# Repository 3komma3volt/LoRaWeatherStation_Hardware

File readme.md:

# LoRa Weather Station

The project was born for testing LoRa devices an has grown to a small weather station ecosystem.
Since August 2002, there are 6 station outside running without any maintenance. 

## Features

 - Completely 3D printed main body
 - Modular with optional extension
 - Simple PCB which can be hand assembled
 - Stations can be equipped with sensors as needed, they don't have to be the same kind
 - Using TheThingsStack for receiving data
 - Storage and analysis of data using a PHP framework (other repository)

## Housing

The main housing consists of:
 - Main housing
 - Front door
 - Sensor cover **or** light sensor mount
 - 2x side dust filter fixture
 - Front door dust filter fixture

On the sides and in the front door, there is the possibility to mount some 3mm fleece filters to prevent dust going into the housing and keep bugs out. A disadvantage is, that the inside gets a bit hotter if exposed to the sun.
The best mounting position of the station is 2m from the ground facing north and protected from sun exposure (The solar cell will get enough light to charge the battery).
A 80x55mm 7V solar cell is used to charge the battery. The solar cell is glued to the main body using silicone glue. This works great to keep rain out,
On the bottom is a intended breaking point to mount 12mm screw connectors for external sensors e.g. rain sensor or wind direction sensor.
On the left side is a hole for mounting a SMA connector for the LoRa antenna.
The housing can be mounted on a wall using a hook or screw.

## PCB
The PCB is kept simple, so it can be assembled by hand. It has to be screwed into the main body using **M3x8** (or similar length, there is plenty of space for longer screws)

It is possible to use it just as carrier board, in this case, no component needs to be assembled.
For easier installation, XH connectors are used to connect sensors, battery, solar cell etc.
The CubeCell AB01 board is the brain of the weather station. It has a battery connector on its bottom side. For easier replacement of board or battery, this connector is connected with the PCB which again connects to the battery.
A BME280 board is connected using a standard header, so it can be replaced easily.

Two holes on the lower side of the PCB are for mounting a lithium battery using zip ties.
A  standard 1000mA 3.7V LIPO battery works great and never ran out even on cold and dark winter weeks.

## Wind Direction Sensor

The wind direction sensor uses 8 reed contacts, a I2C port expander, a bearing (**608ZZ**) and a paddle to read the wind direction.

Only the expander and some few components need to be assembled.

The reed contacts are pushed through the sensor main body, On the upper side, a short wire has to be soldered to the reed contact and threaded through the second hole. The sensor and wire are then soldered to the sensor PCB.
A ⌀6x3mm magnet is glued into the sensor pin.

## Wind Speed Sensor

The wind speed sensor using the same style bearing and manget like the direction sensor. It only consists of one reed contact. 
This sensor is an early alpha state, because the baring is to difficult to move and won't turn on low wind speeds. Maybe switching to a off-the-shelf product for this use case.

## Rain sensor

The 3D printed version of a rain sensor was not reliable enough. A cheap off the shelf sensor which is sold as spare part for weather stations works well. 

## Light sensor

A VEML7700 can be mounted on the side of the main body. For this print the mount and install the sensor within the mount. Fill up the space with transparent silicone. It will get watertight and works well. 

# Firmware
The firmware is made using PlatformIO and the Heltec development platform.
Simply open with VSCode and edit the platform.ini
You can change following build flags:

- ENABLE_RAINSENSOR=0 ; enables the rain drip sensor
- ENABLE_BRIGHTNESSENSOR=1 ; enables the brightness sensor
- ENABLE_WINDDIRSENSOR=0 ; enables the wind direction sensor
- ENABLE_WINDSPEEDSENSOR=0 ; enables the winds speed sensor
- DEBUG_UART=0  ; enables UART data sending for debug purposes

Enable the functionalities as wanted. 

>  Wind speed and direction are BETA!

As brightness sensor the VEML7700 is used. The BH1750 was also tested, but the results with this sensor were not really great. It was not really possible to get the cheap housing with the light dome watertight and several sensors died after a few days. If you want to use the BH1750, some changes in the code are necessary since this parts were removed.

Then hook up with TheThingsStack. There add a new device and get the neccessary data for OTAA transmission. Insert the information in the src/ttnparams.h file.

You probably will need a payload formatter for each individual weather station, since not all stations must have the same functionallity.

Here is a example formatter:

    function Decoder(bytes, port) {
    var temperature = (bytes[0] << 8 | bytes[1]);
	var humidity = (bytes[2] << 8 | bytes[3]);
    var pressure = ((bytes[4]) << 24) + ((bytes[5]) <<  16) + ((bytes[6]) << 8) + ((bytes[7]));
    var battery = (bytes[8] << 8) | bytes[9];
    var unused = (bytes[10] << 8) | bytes[11]; // formally used for battery percent calculation
    var brightness = (bytes[12] << 8) | bytes[13];
    var rain = bytes[14];
  
    var lux = brightness * 2.1504; // Datasheet: Gain 1/8, 25ms integration time
    lux = Math.round(6.0135e-13 * Math.pow(lux, 4) - 9.3924e-9 * Math.pow(lux, 3) + 8.1488e-5 * Math.pow(lux, 2) + 1.0023 * lux);
 
    var sensorSqure = 10.9 * 4.9; // for round rain sensors: sensorSqure = Math.PI * pow(sensorRadius, 2);
    var tipsPer100ml = 100 / 1.5;
    var mlPerTip = 100 / $tipsPer100ml;
    var rainAmount = $mlPerTip / $sensorSqure;
  
    return {
      temperature: temperature / 100,
      humidity: humidity,
      pressure: pressure / 100,
      battery: battery / 1000,
      brightness: lux,
      rain: rainAmount
      }
    }

If a station doesnt have a specific feature, just remove it from the return. The value has to be null to indicate, that the sensor is not available.

Example formatter for the most basic station just with a BME280:

    function Decoder(bytes, port) {
    var temperature = (bytes[0] << 8 | bytes[1]);
	var humidity = (bytes[2] << 8 | bytes[3]);
    var pressure = ((bytes[4]) << 24) + ((bytes[5]) <<  16) + ((bytes[6]) << 8) + ((bytes[7]));
    var battery = (bytes[8] << 8) | bytes[9];
    var unused = (bytes[10] << 8) | bytes[11]; // formally used for battery percent calculation

    return {
      temperature: temperature / 100,
      humidity: humidity,
      pressure: pressure / 100,
      battery: battery / 1000,
      }
    }

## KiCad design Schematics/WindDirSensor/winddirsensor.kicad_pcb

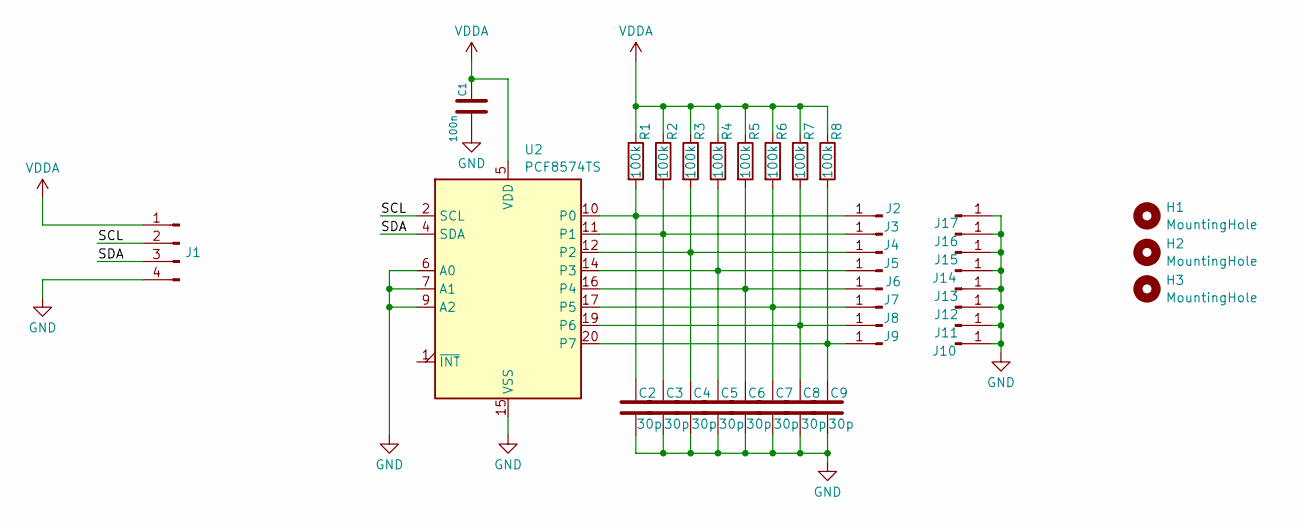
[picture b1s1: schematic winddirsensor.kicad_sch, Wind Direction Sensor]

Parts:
C1: 100n; C_0603_1608Metric; LCSC C14663
C2, C3, C4, C5, C6, C7, C8, C9: 30p; C_0603_1608Metric_Pad1.08x0.95mm_HandSolder; LCSC C1658
H1, H2, H3: MountingHole; MountingHole_3.2mm_M3
J1: Conn_01x04_Pin; JST_XH_B4B-XH-A_1x04_P2.50mm_Vertical
J2, J3, J4, J5, J6, J7, J8, J9, J10, J11, J12, J13, J14, J15, J16, J17: Conn_01x01_Pin; TestPoint_THTPad_D1.5mm_Drill0.7mm
R1, R2, R3, R4, R5, R6, R7, R8: 100k; R_0603_1608Metric; LCSC C25803
U2: PCF8574TS; SSOP-20_4.4x6.5mm_P0.65mm

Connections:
/SCL: J1.2, U2.2 (SCL)
/SDA: J1.3, U2.4 (SDA)
GND: C1.2, C2.2, C3.2, C4.2, C5.2, C6.2, C7.2, C8.2, C9.2, J1.4, J10.1, J11.1, J12.1, J13.1, J14.1, J15.1, J16.1, J17.1, U2.6 (A0), U2.7 (A1), U2.9 (A2), U2.15 (VSS)
unnamed: C2.1, J2.1, R1.2, U2.10 (P0)
unnamed: C3.1, J3.1, R2.2, U2.11 (P1)
unnamed: C4.1, J4.1, R3.2, U2.12 (P2)
unnamed: C5.1, J5.1, R4.2, U2.14 (P3)
unnamed: C6.1, J6.1, R5.2, U2.16 (P4)
unnamed: C7.1, J7.1, R6.2, U2.17 (P5)
unnamed: C8.1, J8.1, R7.2, U2.19 (P6)
unnamed: C9.1, J9.1, R8.2, U2.20 (P7)
VDDA: C1.1, J1.1, R1.1, R2.1, R3.1, R4.1, R5.1, R6.1, R7.1, R8.1, U2.5 (VDD)

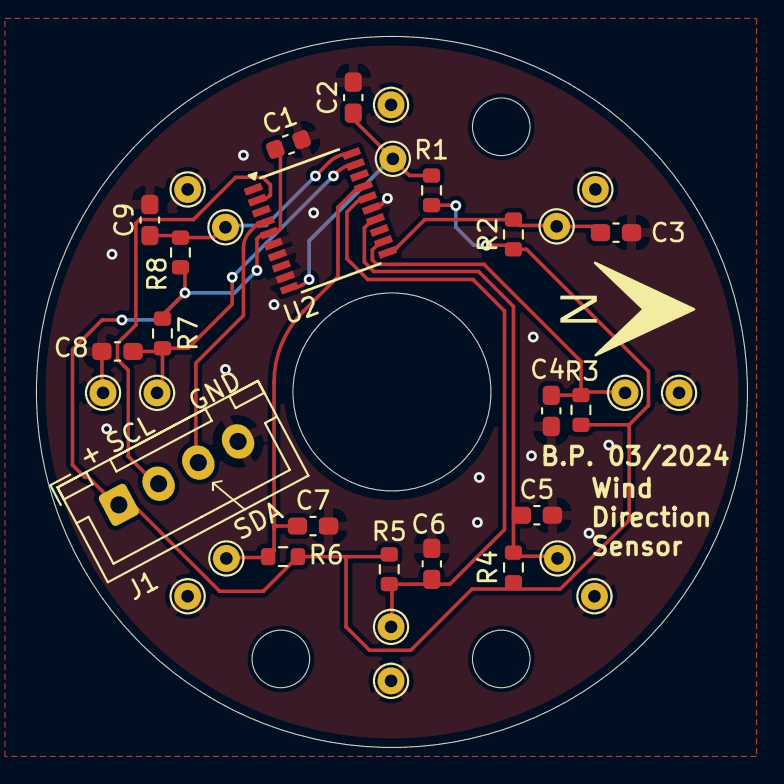
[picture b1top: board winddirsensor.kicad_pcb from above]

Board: 2 copper layers, 39.5 x 39.5 mm, 38 parts (0 on the bottom side), 12 nets.

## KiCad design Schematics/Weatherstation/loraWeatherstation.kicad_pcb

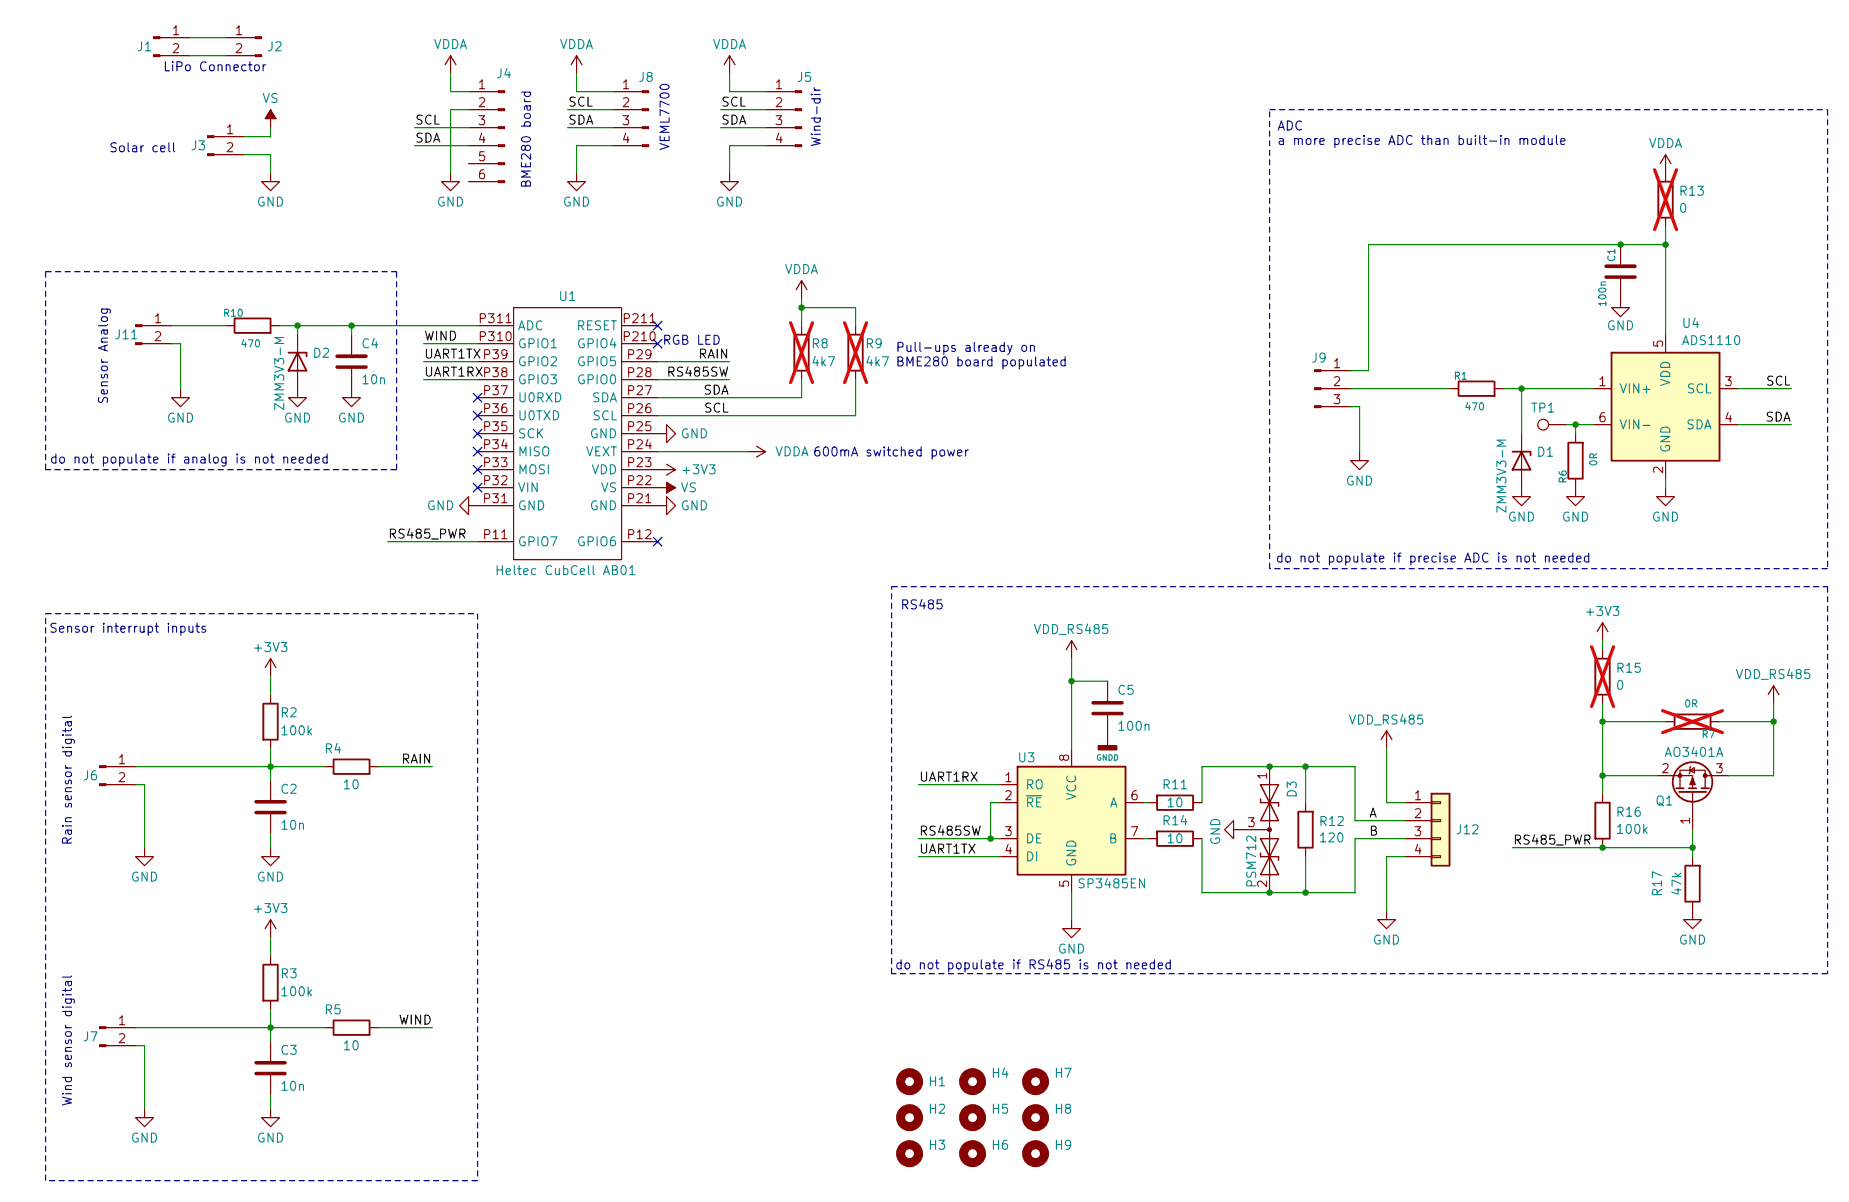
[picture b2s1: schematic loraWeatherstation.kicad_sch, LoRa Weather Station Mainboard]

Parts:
C1, C5: 100n; C_0603_1608Metric; LCSC C14663
C2, C3, C4: 10n; C_0603_1608Metric; LCSC C57112
D1, D2: ZMM3V3-M; D_MiniMELF; LCSC C8056
D3: PSM712; SOT-23; LCSC C32677
H1, H2, H3, H4, H5, H6: MountingHole; MountingHole_3.2mm_M3
H7, H8, H9: MountingHole; MountingHole_2.7mm
J1, J2, J3, J6, J7, J11: Conn_01x02_Pin; JST_XH_B2B-XH-A_1x02_P2.50mm_Vertical
J4: Conn_01x06_Pin; PinSocket_1x06_P2.54mm_Vertical
J5, J8: Conn_01x04_Pin; JST_XH_B4B-XH-A_1x04_P2.50mm_Vertical
J9: Conn_01x03_Pin; JST_XH_B3B-XH-A_1x03_P2.50mm_Vertical
J12: Conn_01x04; JST_XH_B4B-XH-A_1x04_P2.50mm_Vertical
Q1: AO3401A; SOT-23; LCSC C15127
R1, R10: 470; R_0603_1608Metric; LCSC C23182
R2, R3: 100k; R_0603_1608Metric; LCSC C25803
R4, R5, R11, R14: 10; R_0603_1608Metric; LCSC C22859
R6: 0R; R_0603_1608Metric
R7: 0R; R_0603_1608Metric; not fitted
R8, R9: 4k7; R_0603_1608Metric; LCSC C23162; not fitted
R12: 120; R_0603_1608Metric; LCSC C22787
R13, R15: 0; R_0603_1608Metric; not fitted
R16: 100k; R_0603_1608Metric; LCSC C22936
R17: 47k; R_0603_1608Metric; LCSC C25819
TP1: TestPoint; TestPoint_Pad_D1.5mm
U1: Heltec CubCell AB01; CubeCellAB01
U3: SP3485EN; SOIC-8_3.9x4.9mm_P1.27mm; LCSC C8963
U4: ADS1110; SOT-23-6

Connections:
+3V3: R2.1, R3.1, R15.1, U1.P23 (VDD)
/A: D3.1 (A1), J12.2, R11.1, R12.2
/B: D3.2 (A2), J12.3, R12.1, R14.1
/RAIN: R4.2, U1.P29 (GPIO5)
/RS485SW: U1.P28 (GPIO0), U3.2 (~RE), U3.3 (DE)
/RS485_PWR: Q1.1 (G), R16.2, R17.2, U1.P11 (GPIO7)
/SCL: J4.3, J5.2, J8.2, R9.2, U1.P26 (SCL), U4.3 (SCL)
/SDA: J4.4, J5.3, J8.3, R8.2, U1.P27 (SDA), U4.4 (SDA)
/UART1RX: U1.P38 (GPIO3), U3.1 (RO)
/UART1TX: U1.P39 (GPIO2), U3.4 (DI)
/WIND: R5.2, U1.P310 (GPIO1)
GND: C1.2, C2.2, C3.2, C4.2, D1.2 (A), D2.2 (A), D3.3 (common), J3.2, J4.2, J5.4, J6.2, J7.2, J8.4, J9.3, J11.2, J12.4, R6.1, R17.1, U1.P21 (GND), U1.P25 (GND), U1.P31 (GND), U3.5 (GND), U4.2 (GND)
GNDD: C5.2
unnamed: D1.1 (K), R1.2, U4.1 (VIN+)
unnamed: C4.1, D2.1 (K), R10.2, U1.P311 (ADC)
unnamed: J1.1, J2.1
unnamed: J1.2, J2.2
unnamed: C2.1, J6.1, R2.2, R4.1
unnamed: C3.1, J7.1, R3.2, R5.1
unnamed: C1.1, J9.1, R13.2, U4.5 (VDD)
unnamed: J9.2, R1.1
unnamed: J11.1, R10.1
unnamed: Q1.2 (S), R7.2, R15.2, R16.1
unnamed: R11.2, U3.6 (A)
unnamed: R14.2, U3.7 (B)
unnamed: R6.2, TP1.1, U4.6 (VIN-)
VDDA: J4.1, J5.1, J8.1, R8.1, R9.1, R13.1, U1.P24 (VEXT)
VDD_RS485: C5.1, J12.1, Q1.3 (D), R7.1, U3.8 (VCC)
VS: J3.1, U1.P22 (VS)

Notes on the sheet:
do not populate if precise ADC is not needed
Rain sensor digital
ADC a more precise ADC than built-in module
do not populate if RS485 is not needed
Solar cell
Pull-ups already on BME280 board populated
Sensor interrupt inputs
do not populate if analog is not needed
RS485
RGB LED
BME280 board
600mA switched power
Wind-dir
Wind sensor digital
LiPo Connector
Sensor Analog
VEML7700

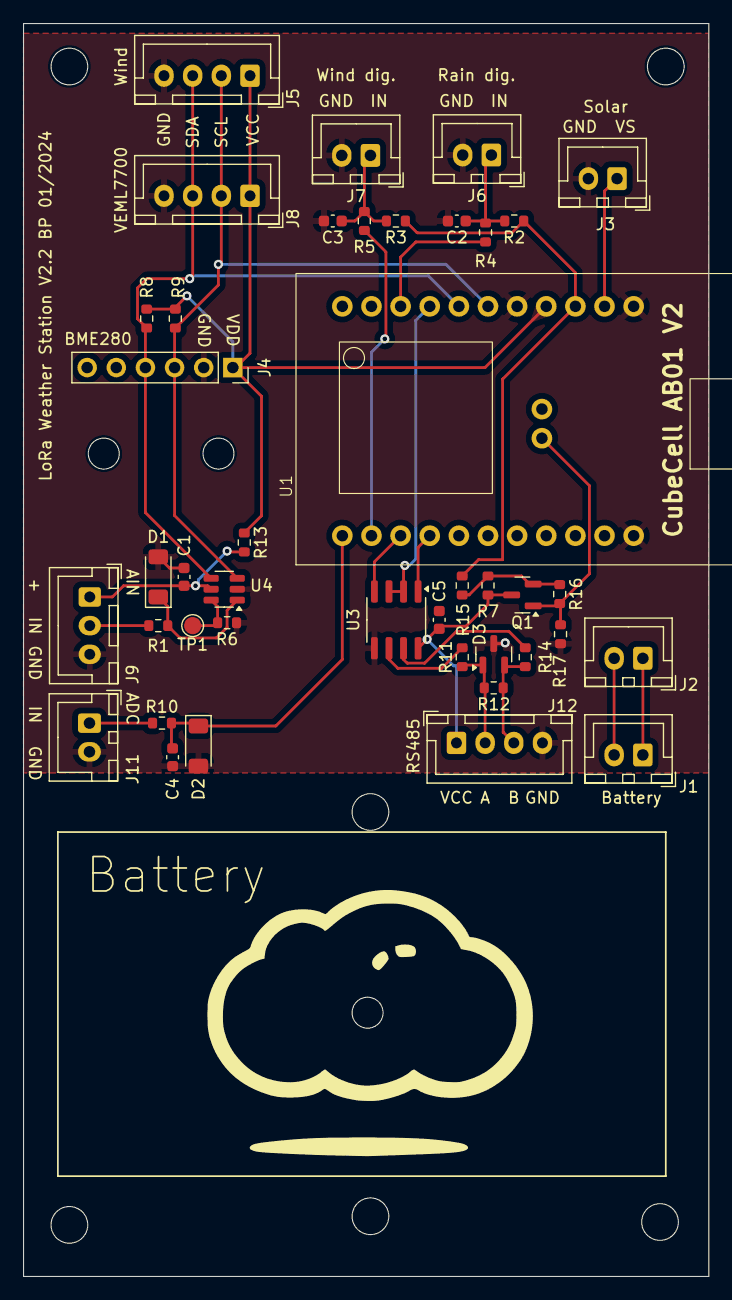
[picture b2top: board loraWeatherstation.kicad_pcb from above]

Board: 2 copper layers, 59.8 x 109.2 mm, 50 parts (0 on the bottom side), 28 nets.

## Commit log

2025-01-07 Fixed printing of undefined sensors
2025-10-12 Improved front door filter mount for better mount Made VEML7700 a bit higher for better water tightness
